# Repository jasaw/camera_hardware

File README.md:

# Raspberry Pi based security camera hardware

Outdoor Raspberry Pi Zero W security camera

## Software

If you don't already have software to run on this camera, [motionEyeOS](https://github.com/jasaw/motioneyeos/releases) is a good one to try.

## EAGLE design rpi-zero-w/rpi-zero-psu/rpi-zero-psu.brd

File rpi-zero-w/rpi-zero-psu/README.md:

# Raspberry Pi Zero power supply

Power supply board that plugs directly onto a Raspberry Pi Zero (W)

Features:
* Input: 9V to 24V DC
* Output: 5V 3A to the RPi
* Basic light sensor circuit ([LDR reader software here](https://github.com/jasaw/ldr-reader))
* One GPIO controlled output (5V 1A)

### Design files

* [Gerbers](rpi-zero-psu-rev-1a.zip)
* [PCB top](rpi-zero-psu-rev-1a-top.pdf)
* [PCB bottom](rpi-zero-psu-rev-1a-bottom.pdf)

### Bill of Materials

* [BoM](rpi-zero-psu-rev-1a-bom.pdf)
* 3A XM1584 DC-DC step-down module can be sourced from other places:
  * [Seeed Studio](https://www.seeedstudio.com/Adjustable-Step-Down-DC%26DC-Converter-%280.8V-18V%263A%29-p-1716.html)
  * [AliExpress](https://www.aliexpress.com/item/Free-Shipping-5PCS-XM1584-Ultra-small-size-DC-DC-step-down-power-supply-module-3A-adjustable/32262690691.html)
  * [AliExpress](https://www.aliexpress.com/item/10pcs-lot-Ultra-Small-Size-DC-DC-Step-Down-Power-Supply-Module-3A-Adjustable-Step-Down/32478748937.html)

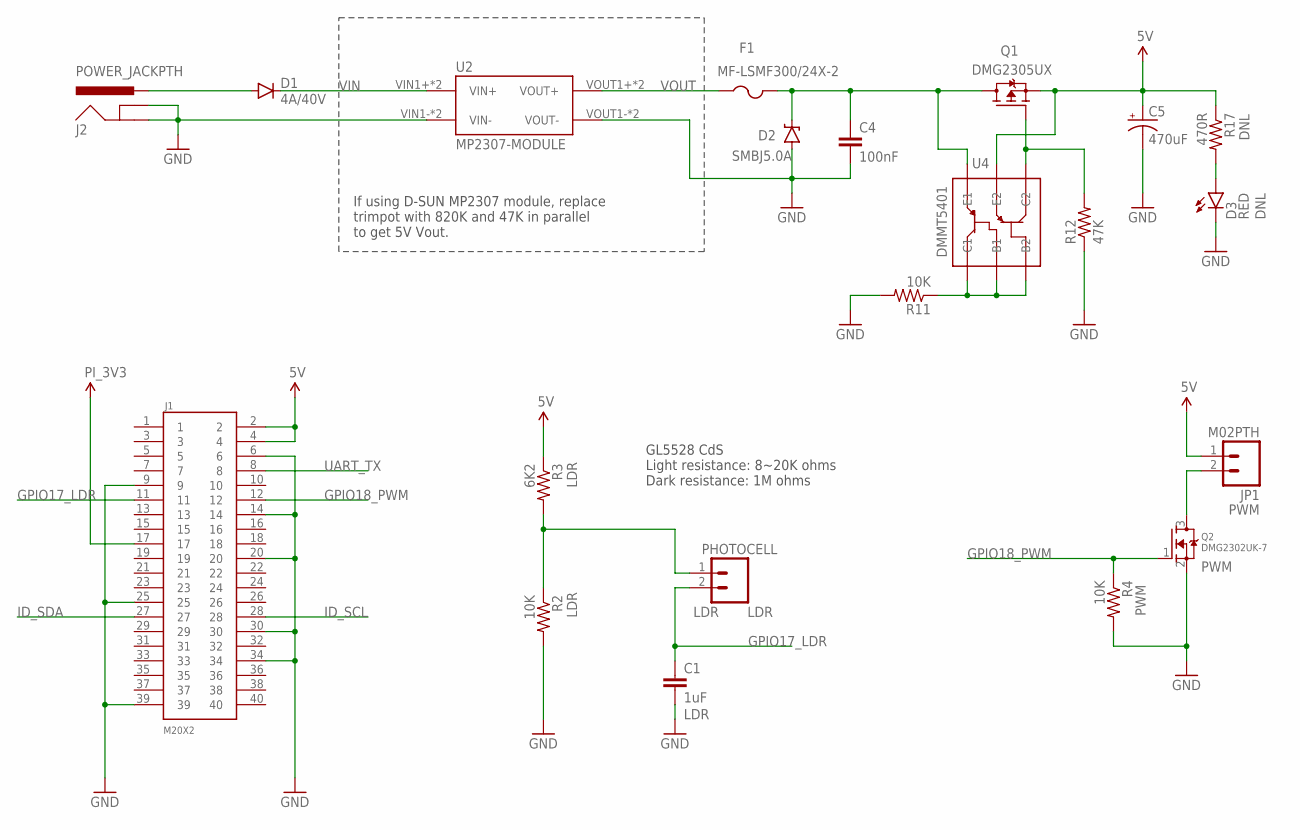
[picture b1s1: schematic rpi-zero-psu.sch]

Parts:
C1: 1uF; 0805; PARTNO CC0805KKX7R8BB105; DIGIKEY 311-1456-1-ND
C4: 100nF; 0805; PARTNO 08055C104KAT2A; DIGIKEY 478-1395-1-ND
C5: 470uF; PANASONIC_F; PARTNO 875115150005; DIGIKEY 732-6443-1-ND
D1: 4A/40V; SMC; PARTNO MBRS340T3G; DIGIKEY MBRS340T3GOSCT-ND
D2: SMBJ5.0A; SMB-DIODE; PARTNO SMBJ5.0A; DIGIKEY SMBJ5.0ALFCT-ND
D3: RED; LED-1206; PARTNO LTST-C150CKT; DIGIKEY 160-1167-1-ND
F1: MF-LSMF300/24X-2; 2920; PARTNO MF-LSMF300/24X-2; DIGIKEY MF-LSMF300/24X-2CT-ND
J1: M20X2; 2X20; PARTNO PPPC202LFBN-RC; DIGIKEY S7123-ND
J2: POWER_JACKPTH; POWER_JACK_PTH; PARTNO PJ-002A; DIGIKEY CP-002A-ND
JP1: M02PTH; 1X02; PARTNO 826936-2; MOUSER 571-826936-2
LDR: PHOTOCELL; 1X02_NO_SILK
Q1: DMG2305UX; SOT-23; PARTNO DMG2305UX-7; DIGIKEY DMG2305UX-7DICT-ND
Q2: DMG2302UK-7; SOT23; PARTNO DMG2302UK-7; DIGIKEY DMG2302UK-7DICT-ND
R2, R4, R11: 10K; 0805; PARTNO RC0805JR-0710KL; DIGIKEY 311-10KARCT-ND
R3: 6K2; 0805; PARTNO RC0805JR-076K2L; DIGIKEY 311-6.2KARCT-ND
R12: 47K; 0805; PARTNO RC0805FR-0747KL; DIGIKEY 311-47.0KCRCT-ND
R17: 470R; 0805; PARTNO RC0805JR-07470RL; DIGIKEY 311-470ARCT-ND
U2: MP2307-MODULE; MP1584EN-MODULE; PARTNO 106990005; DIGIKEY 106990005-ND
U4: DMMT5401; SOT23-6; PARTNO DMMT5401-7-F; DIGIKEY DMMT5401-FDICT-ND

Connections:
3.3V: J1.17
5V: C5.+, J1.2, J1.4, JP1.1, Q1.2 (S), R3.1, R17.1, U4.5 (E2)
GND: C1.2, C4.2, C5.-, D2.A, D3.C, J1.6, J1.9, J1.14, J1.20, J1.25, J1.30, J1.34, J1.39, J2.GND, J2.GNDBREAK, Q2.2 (S), R2.2, R4.2, R11.2, R12.1, U2.VIN1- (VIN-), U2.VIN2- (VIN-), U2.VOUT1- (VOUT-), U2.VOUT2- (VOUT-)
GPIO17_LDR: C1.1, J1.11, LDR.2
GPIO18_PWM: J1.12, Q2.1 (G), R4.1
ID_SCL: J1.28
ID_SDA: J1.27
unnamed: JP1.2, Q2.3 (D)
unnamed: LDR.1, R2.1, R3.2
unnamed: D3.A, R17.2
unnamed: D1.A, J2.PWR
unnamed: C4.1, D2.C, F1.2, Q1.3 (D), U4.6 (E1)
unnamed: R11.1, U4.1 (C1), U4.2 (B1), U4.3 (B2)
unnamed: Q1.1 (G), R12.2, U4.4 (C2)
UART_TX: J1.8
VIN: D1.C, U2.VIN1+ (VIN+), U2.VIN2+ (VIN+)
VOUT: F1.1, U2.VOUT1+ (VOUT+), U2.VOUT2+ (VOUT+)

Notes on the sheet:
If using D-SUN MP2307 module, replace trimpot with 820K and 47K in parallel to get 5V Vout.
GL5528 CdS Light resistance: 8~20K ohms Dark resistance: 1M ohms

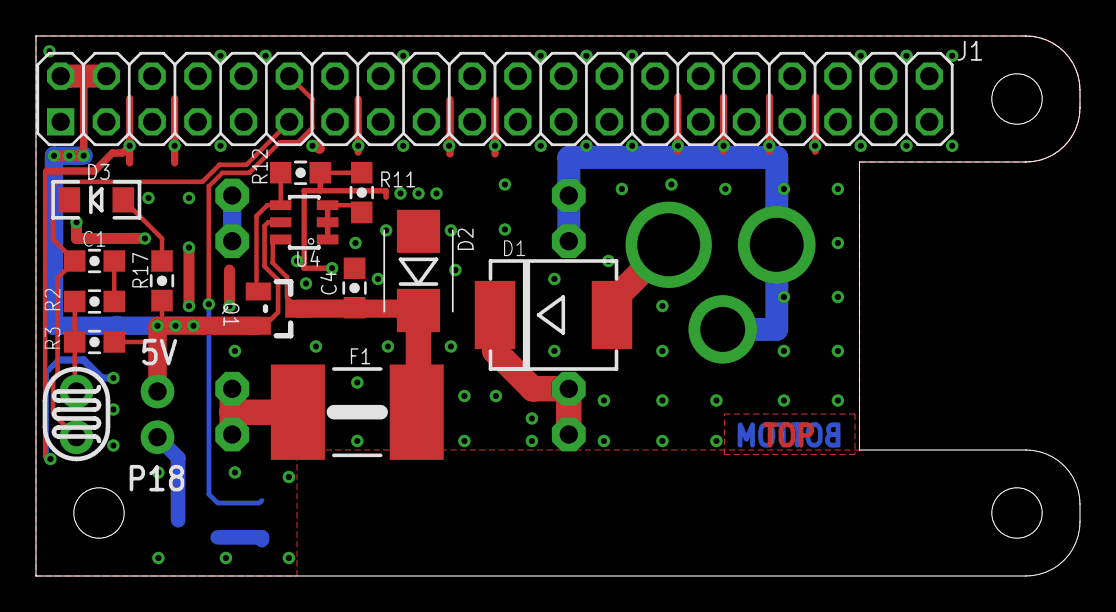
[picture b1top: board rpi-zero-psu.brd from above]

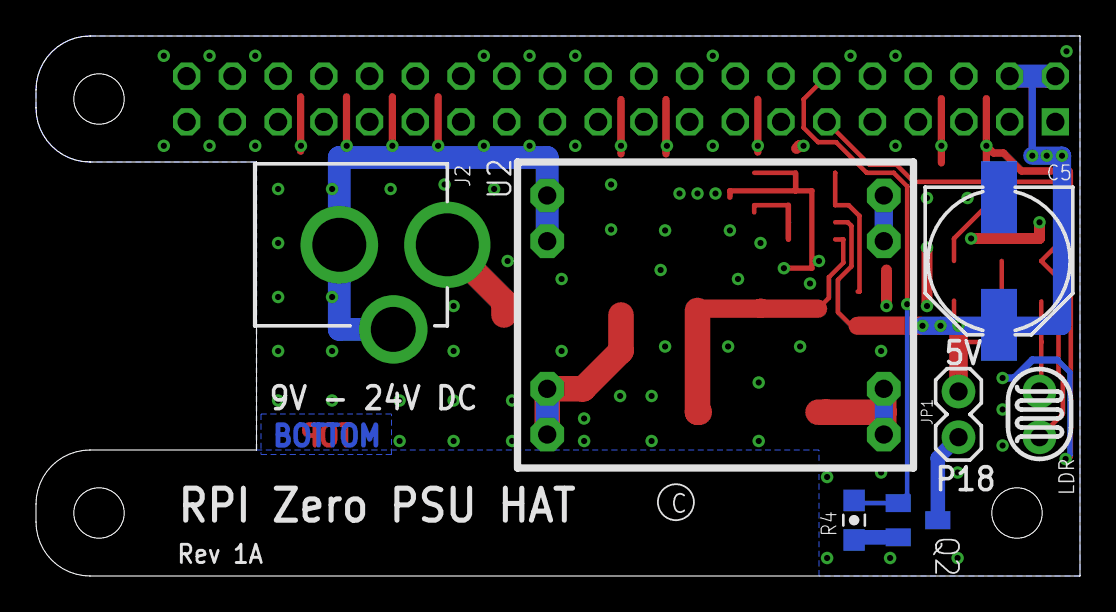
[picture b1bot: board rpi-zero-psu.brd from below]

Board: 2 copper layers, 58.0 x 30.0 mm, 21 parts (7 on the bottom side), 13 nets.

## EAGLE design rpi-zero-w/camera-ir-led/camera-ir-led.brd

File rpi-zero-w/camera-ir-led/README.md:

# IR-LED board

IR-LED board for night vision.

Current issues:
* IR light is not bright enough to illuminate large area
  * As a workaround, use [external IR LEDs](https://www.aliexpress.com/item/Free-shipping-48LEDs-Illuminator-IR-Infrared-dome-CCTV-camera-hd-Night-enhancement-Fill-light-Vision-40M/32811672765.html).

### Design files

* [Gerbers](camera-ir-led-rev-1a.zip)
* [PCB top](camera-ir-led-rev-1a-top-parts.pdf)
* [PCB bottom](camera-ir-led-rev-1a-bottom-parts.pdf)

### Bill of Materials

* [BoM](camera-ir-led-rev-1a.xlsx)
* 5mm IR LEDs 940nm Wave Length
  * Forward Voltage: 1.5~1.6V
  * Forward Current: 60mA Continuous, 120mA peak 10% pulse width
  * View Angle: 15-30 degree
  * [ebay](https://www.ebay.com.au/itm/100pcs-5mm-LED-Lights-Infrared-Emitters-IR-Emitting-Diodes-940nm-Wave-Length/201201649166)
* 5mm IR LEDs 850nm Wave Length
  * Forward Voltage: 1.45~1.65V
  * Forward Current: 20mA Continuous, 100mA max pulse
  * View Angle: 30 degree
  * [AliExpress](https://www.aliexpress.com/item/100Pcs-5mm-IR-Led-850nm-Lamp-Transmitting-Tube-Emitting-Diode-Infrared-LED-Diode-ir-850nm-High/32373548361.html)
* GL5528 LDR Photo Resistors
  * [ebay](http://www.ebay.com.au/itm/20PCS-Photoresistor-GL5528-LDR-Photo-Resistors-Light-Dependent-WS/222122787897)
* JST PH 2.00mm pitch 4-pin connector and cable
  * [AliExpress](https://www.aliexpress.com/item/20-Sets-PH-2-0mm-JST-2-3-4-5-6-7-8-9-10-12P/32782287584.html)
  * [AliExpress](https://www.aliexpress.com/item/20-SETS-Mini-Micro-JST-2-0-PH-4-Pin-Connector-plug-with-Wires-Cables-300MM/32611300648.html)
  * [AliExpress](https://www.aliexpress.com/item/10sets-1-0mm-1-25mm-1-5mm-2-0-2-54mm-2-3-4-5-6/32733307616.html)
* Optical IR Cut Light Filter 8mm (for LDR light sensor)
  * [ebay](https://www.ebay.com.au/itm/10pcs-Optical-UV-IR-Cut-Light-Filter-Blocking-For-Camera-Astronomy-Lens-8mm-Slim/282653207704)
* Some heatshrink to hold the IR Cut Light Filter

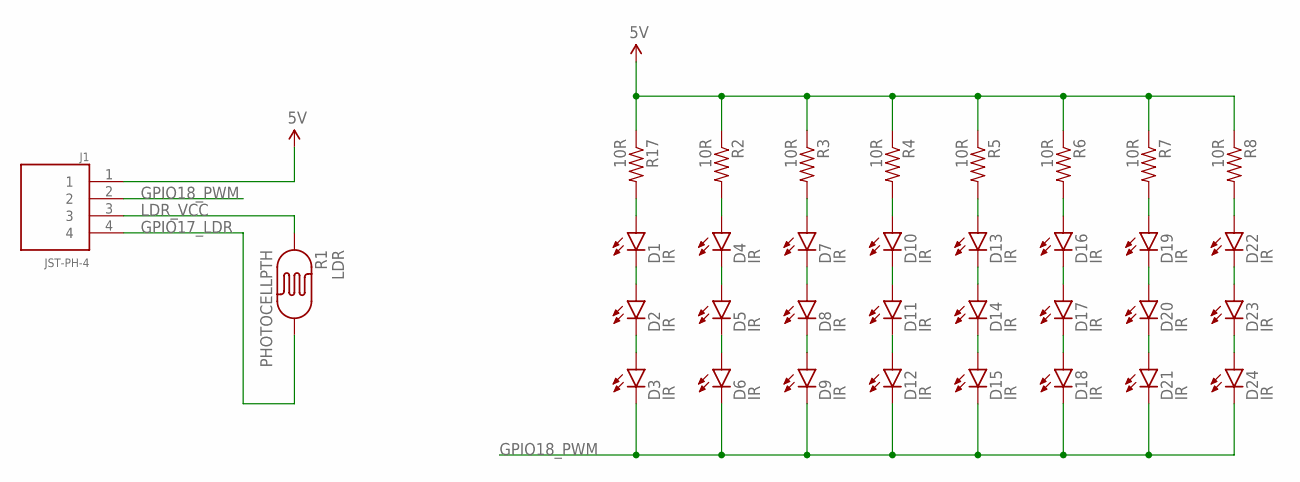
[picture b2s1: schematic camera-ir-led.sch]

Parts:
D1, D2, D3, D4, D5, D6, D7, D8, D9, D10, D11, D12, D13, D14, D15, D16, D17, D18, D19, D20, D21, D22, D23, D24: IR; LED5MM
J1: JST-PH-4; JST-PH-4-POS-TH
R1: PHOTOCELLPTH; PHOTOCELL; PARTNO GL5528
R2, R3, R4, R5, R6, R7, R8, R17: 10R; 0805; PARTNO RC0805JR-0710RL; DIGIKEY 311-10ARCT-ND

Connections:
5V: J1.1, R2.1, R3.1, R4.1, R5.1, R6.1, R7.1, R8.1, R17.1
GPIO17_LDR: J1.4, R1.2
GPIO18_PWM: D3.K (C), D6.K (C), D9.K (C), D12.K (C), D15.K (C), D18.K (C), D21.K (C), D24.K (C), J1.2
LDR_VCC: J1.3, R1.1
unnamed: D2.K (C), D3.A
unnamed: D1.K (C), D2.A
unnamed: D1.A, R17.2
unnamed: D5.K (C), D6.A
unnamed: D4.K (C), D5.A
unnamed: D4.A, R2.2
unnamed: D8.K (C), D9.A
unnamed: D7.K (C), D8.A
unnamed: D7.A, R3.2
unnamed: D11.K (C), D12.A
unnamed: D10.K (C), D11.A
unnamed: D10.A, R4.2
unnamed: D14.K (C), D15.A
unnamed: D13.K (C), D14.A
unnamed: D13.A, R5.2
unnamed: D17.K (C), D18.A
unnamed: D16.K (C), D17.A
unnamed: D16.A, R6.2
unnamed: D20.K (C), D21.A
unnamed: D19.K (C), D20.A
unnamed: D19.A, R7.2
unnamed: D23.K (C), D24.A
unnamed: D22.K (C), D23.A
unnamed: D22.A, R8.2

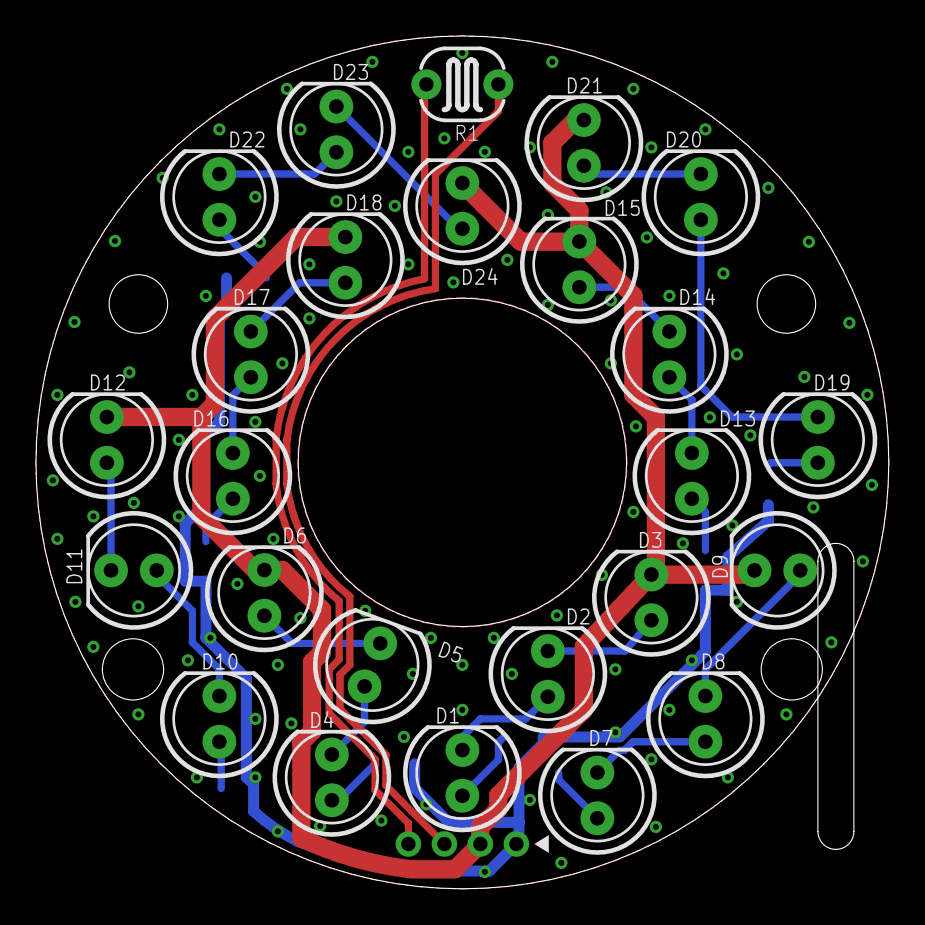
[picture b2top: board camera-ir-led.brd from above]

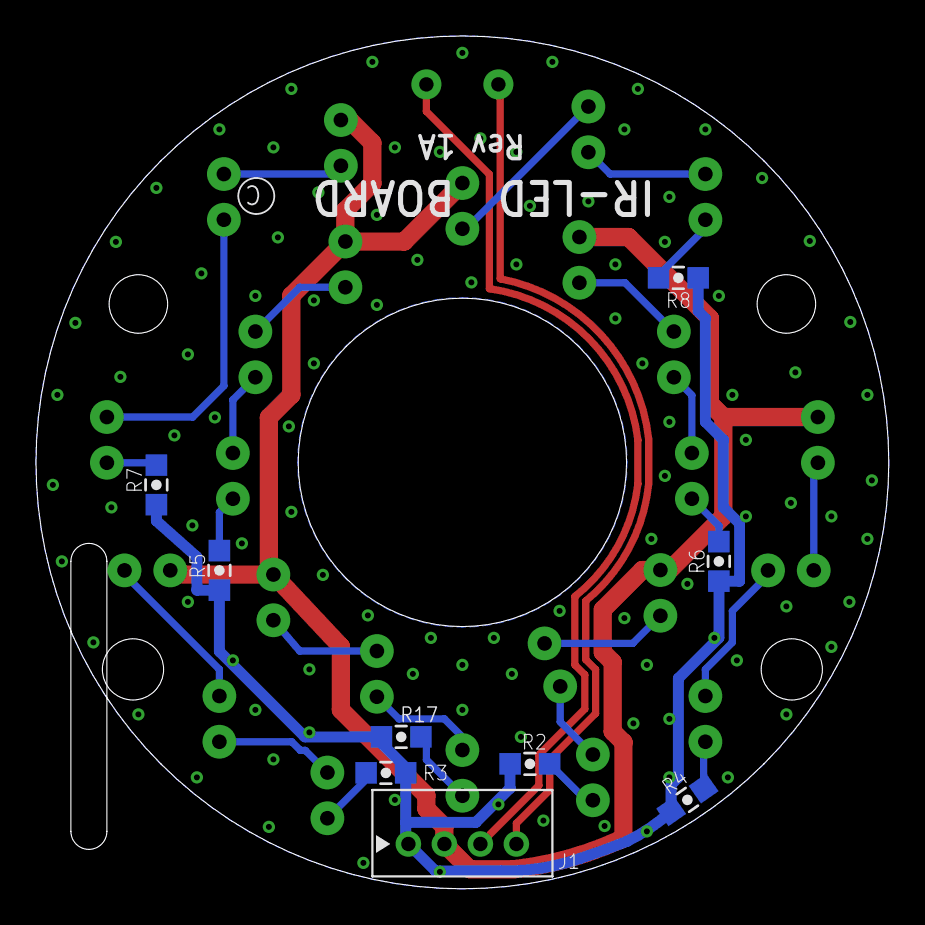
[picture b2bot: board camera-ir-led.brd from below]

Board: 2 copper layers, 47.4 x 47.4 mm, 34 parts (9 on the bottom side), 28 nets.

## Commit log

2017-10-20 add rpi zero w camera bracket
2017-10-24 add IR LED board
2017-10-25 moved IR LEDs
2017-10-26 add rev 1 gerbers
2018-01-12 add camera shroud 3D model
2018-03-27 modified camera bracket for rpi-zero-psu
2018-03-27 camera bracket: improve IR board mount
2018-03-28 camera bracket: add UM2 normal quality gcode
2018-04-03 add rpi-zero power supply hat
2018-04-09 added camera shroud model into bracket design
2018-04-09 add camera shroud foam model
2018-04-09 add assembly diagram
2018-04-17 rpi-zero-psu: removed milling layer
2018-06-22 Updated documentation
2018-06-25 more doco

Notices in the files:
parts and their libraries:
SparkFun-Passives: Licensing: Creative Commons ShareAlike 4.0 International - https://creativecommons.org/licenses/by-sa/4.0
